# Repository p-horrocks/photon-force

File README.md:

# photon-force

A laser tag implementation using the Particle Photon as the main processor.

# Compiling

To compile this project locally you'll need the gcc-arm toolchain as well as the
Photon firmware. It's built against firmware 0.4.9

* If you get permission problems running npm, see here:
https://docs.npmjs.com/getting-started/fixing-npm-permissions

(On Debian)
> apt-get install gcc-arm-none-eabi dfu_util npm
> npm install -g particle-cli
> git clone https://github.com/spark/firmware.git
> cd firmware
> git checkout release/v0.4.9

Next, create a symlink in firmware/user/applications to where this source is
checked out.

# Flashing

Plug the Photon into a USB port. Once it has powered up, hold down the setup
button then tap the reset button. The status LED will flash magenta for a few
seconds then flash yellow, release the setup button. With the LED flashing
yellow run 'make install' and the firmware will be uploaded using dfu.

# Qt Creator

These files are the Qt Creator project files, they're not needed to compile
the project, they just make is easier to use Qt Creator as the IDE:

  photon-force.config
  photon-force.creator
  photon-force.files
  photon-force.includes

# Gerber generation

From within PCBNew:
- File->Plot
- Plot format: Gerber
- Check Layers
    F.Cu
    B.Cu
    F.SilkS
    B.SilkS
    F.Mask
    B.Mask
    Edge.Cuts
- Check Options
    Plot module value on silkscreen
    Plot module reference on silkscreen
    Plot other module texts on silkscreen
    Exclude PCB edge layer from other layers
    Default line width 0.15mm
- Check Gerber Options
    Use proper filename extensions
- Click 'Plot'
- Click 'Generate Drill File'
- Check Drill Units: Inches
- Check Zeros Format: Decimal format
- Check Drill Map File Format: Gerber
- Check Options: Minimal header
- Check Drill Origin: Absolute
- Click 'Drill File'
- Remove layer names from plot files (so they're all <name>.gXX)
- Rename *.gbr to *.gml
- Rename *.drl to *.txt
- zip with zip -r <zip file> <name>.*
- zip file ready for upload!

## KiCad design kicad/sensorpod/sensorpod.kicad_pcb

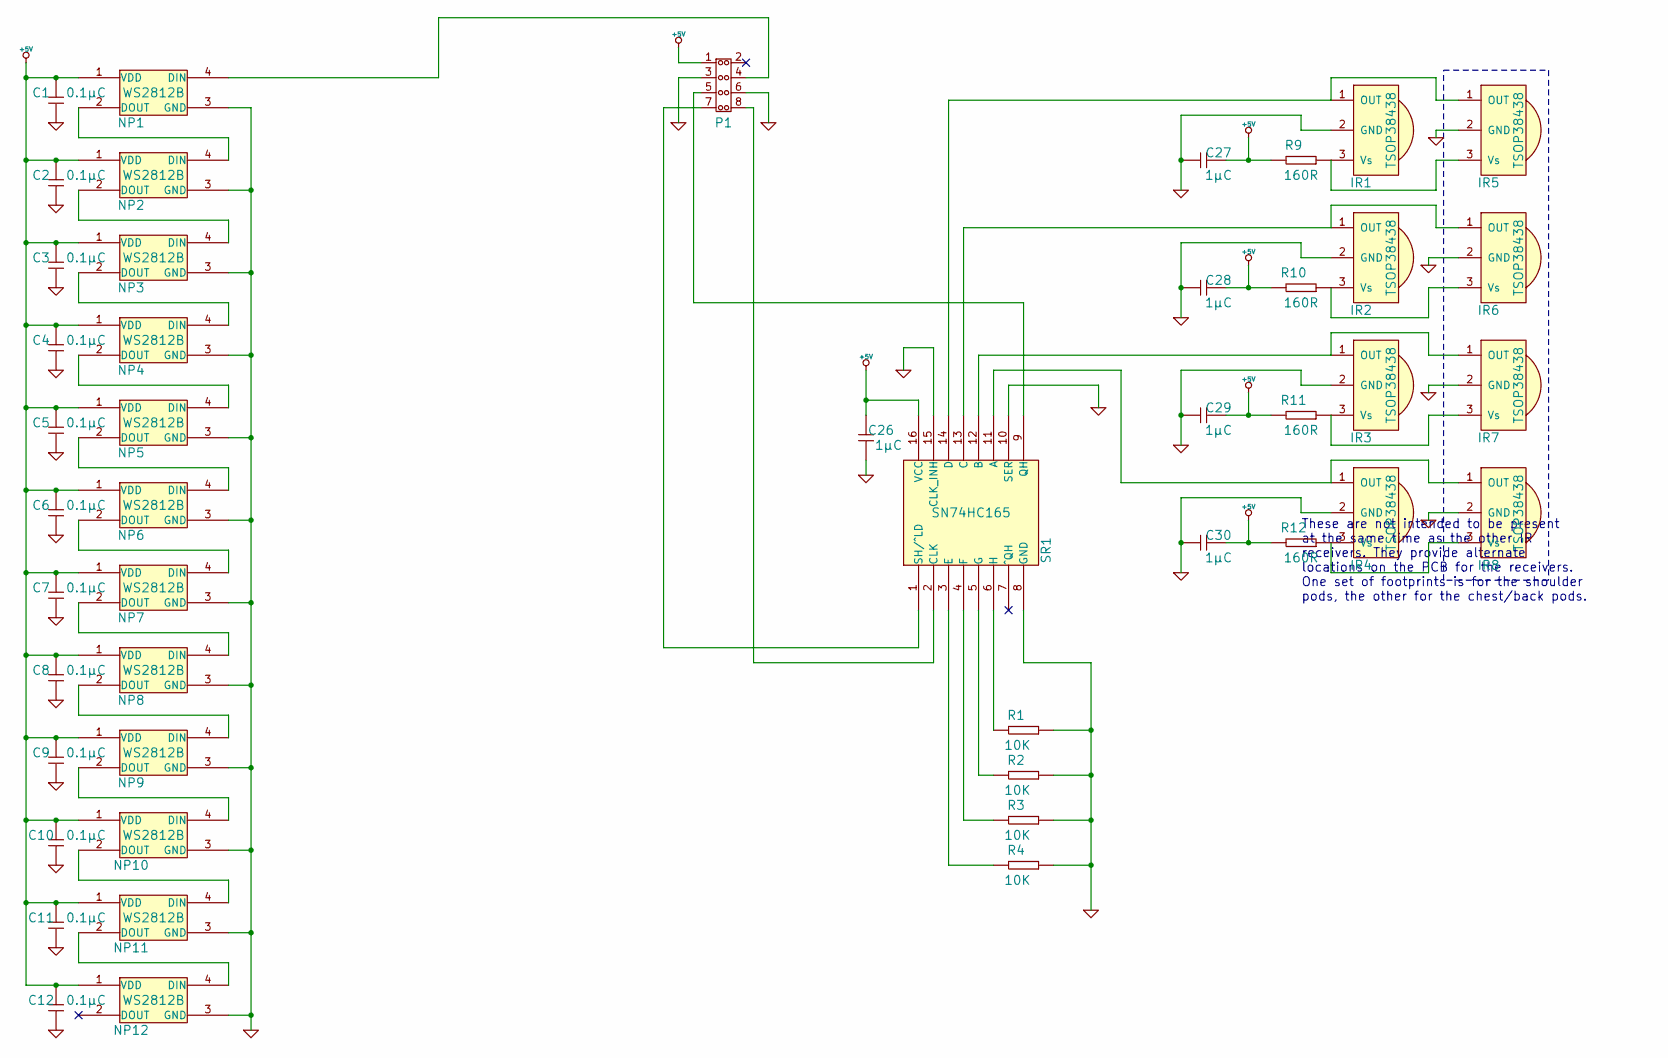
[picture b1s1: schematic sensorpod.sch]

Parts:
C1, C2, C3, C4, C5, C6, C7, C8, C9, C10, C11, C12, C26, C27, C28, C29, C30: GENERIC_CAPACITOR; 0805
IR1, IR2, IR3, IR4, IR5, IR6, IR7, IR8: TSOP38438; Minicast
NP1, NP2, NP3, NP4, NP5, NP6, NP7, NP8, NP9, NP10, NP11, NP12: WS2812B; 5050
P1: HEADER_(8_WAY); Header_4x2
R1, R2, R3, R4, R9, R10, R11, R12: GENERIC_RESISTOR; 0805
SR1: SN74HC165; SOIC-16

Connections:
+5V: C1.1, C2.1, C3.1, C4.1, C5.1, C6.1, C7.1, C8.1, C9.1, C10.1, C11.1, C12.1, C26.1, C27.1, C28.1, C29.1, C30.1, NP1.1 (VDD), NP2.1 (VDD), NP3.1 (VDD), NP4.1 (VDD), NP5.1 (VDD), NP6.1 (VDD), NP7.1 (VDD), NP8.1 (VDD), NP9.1 (VDD), NP10.1 (VDD), NP11.1 (VDD), NP12.1 (VDD), P1.1, R9.1, R10.1, R11.1, R12.1, SR1.16 (VCC)
GND: C1.2, C2.2, C3.2, C4.2, C5.2, C6.2, C7.2, C8.2, C9.2, C10.2, C11.2, C12.2, C26.2, C27.2, C28.2, C29.2, C30.2, IR1.2 (GND), IR2.2 (GND), IR3.2 (GND), IR4.2 (GND), IR5.2 (GND), IR6.2 (GND), IR7.2 (GND), IR8.2 (GND), NP1.3 (GND), NP2.3 (GND), NP3.3 (GND), NP4.3 (GND), NP5.3 (GND), NP6.3 (GND), NP7.3 (GND), NP8.3 (GND), NP9.3 (GND), NP10.3 (GND), NP11.3 (GND), NP12.3 (GND), P1.3, P1.6, R1.2, R2.2, R3.2, R4.2, SR1.8 (GND), SR1.10 (SER), SR1.15 (CLK_INH)
unnamed: P1.8, SR1.2 (CLK)
unnamed: P1.7, SR1.1 (SH/^LD)
unnamed: NP11.2 (DOUT), NP12.4 (DIN)
unnamed: NP10.2 (DOUT), NP11.4 (DIN)
unnamed: IR2.3 (Vs), IR6.3 (Vs), R10.2
unnamed: IR1.1 (OUT), IR5.1 (OUT), SR1.14 (D)
unnamed: IR4.3 (Vs), IR8.3 (Vs), R12.2
unnamed: IR3.3 (Vs), IR7.3 (Vs), R11.2
unnamed: IR1.3 (Vs), IR5.3 (Vs), R9.2
unnamed: IR4.1 (OUT), IR8.1 (OUT), SR1.11 (A)
unnamed: IR3.1 (OUT), IR7.1 (OUT), SR1.12 (B)
unnamed: IR2.1 (OUT), IR6.1 (OUT), SR1.13 (C)
unnamed: NP1.4 (DIN), P1.4
unnamed: R4.1, SR1.3 (E)
unnamed: R3.1, SR1.4 (F)
unnamed: R2.1, SR1.5 (G)
unnamed: R1.1, SR1.6 (H)
unnamed: P1.5, SR1.9 (QH)
unnamed: NP9.2 (DOUT), NP10.4 (DIN)
unnamed: NP5.2 (DOUT), NP6.4 (DIN)
unnamed: NP4.2 (DOUT), NP5.4 (DIN)
unnamed: NP3.2 (DOUT), NP4.4 (DIN)
unnamed: NP2.2 (DOUT), NP3.4 (DIN)
unnamed: NP1.2 (DOUT), NP2.4 (DIN)
unnamed: NP8.2 (DOUT), NP9.4 (DIN)
unnamed: NP7.2 (DOUT), NP8.4 (DIN)
unnamed: NP6.2 (DOUT), NP7.4 (DIN)

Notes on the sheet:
These are not intended to be present at the same time as the other IR receivers. They provide alternate locations on the PCB for the receivers. One set of footprints is for the shoulder pods, the other for the chest/back pods.

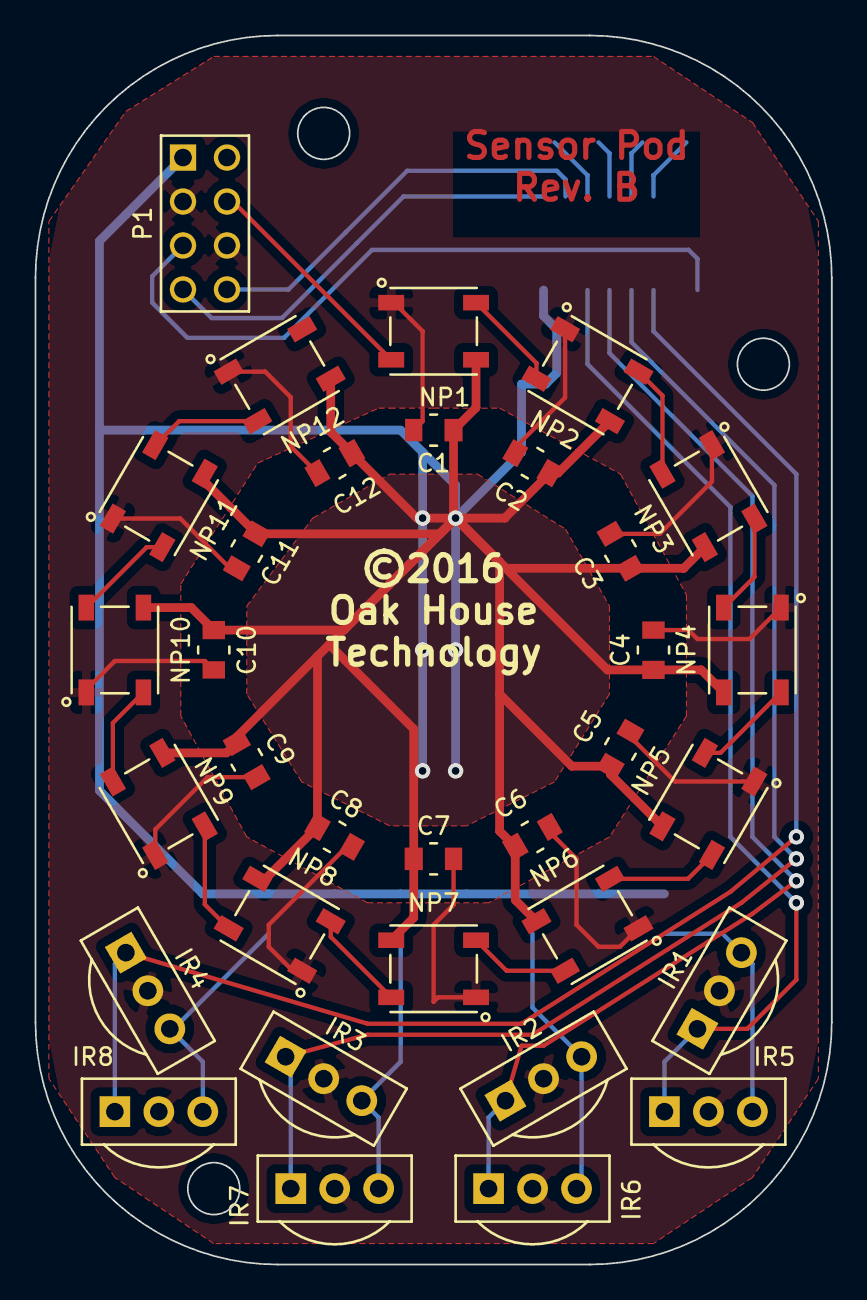
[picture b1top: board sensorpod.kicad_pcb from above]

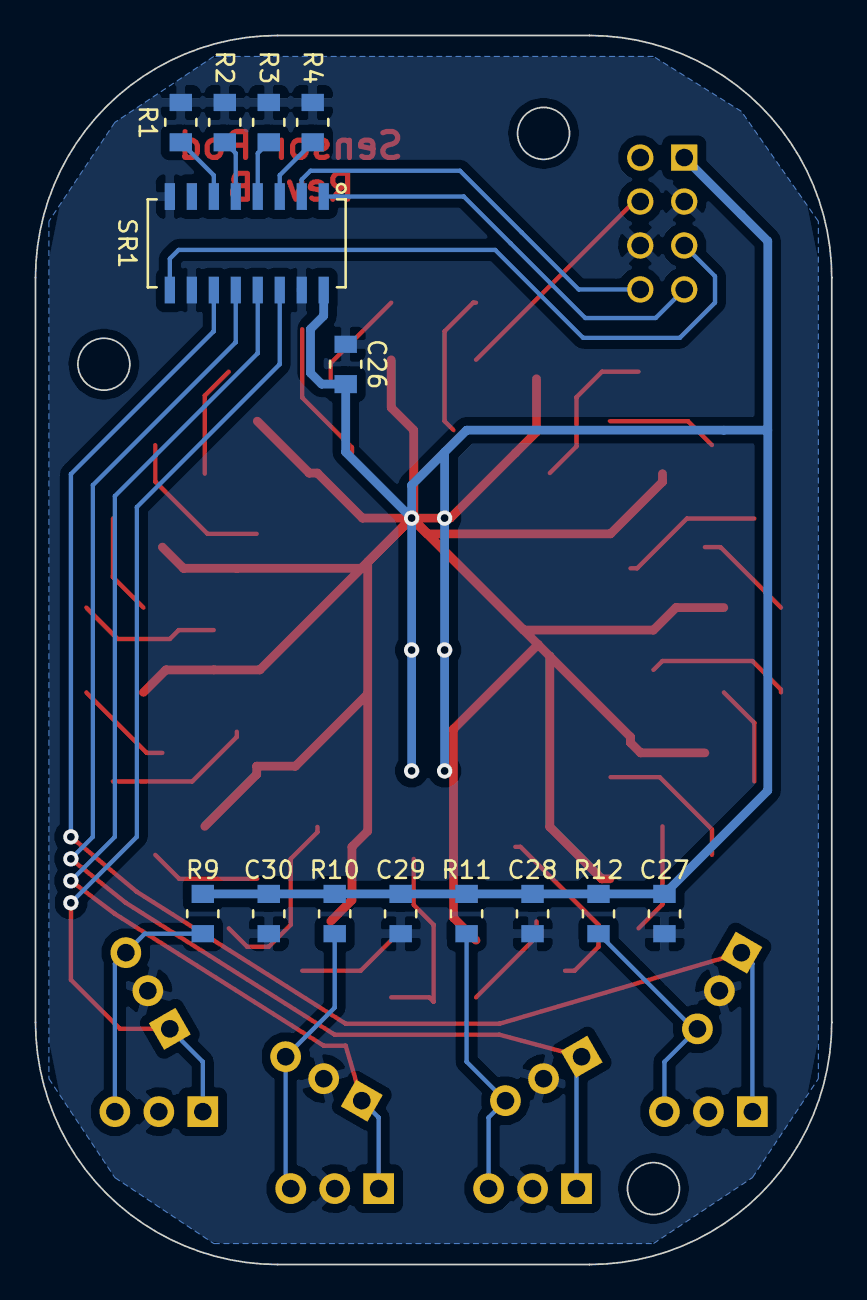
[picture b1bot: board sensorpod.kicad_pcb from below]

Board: 2 copper layers, 46.0 x 71.0 mm, 47 parts (14 on the bottom side), 29 nets.

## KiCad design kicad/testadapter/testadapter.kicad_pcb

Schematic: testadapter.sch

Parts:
P1: HEADER_5X2; Header_5x2
P2, P3, P4, P5: HEADER_(8_WAY); Header_4x2
Q1, Q2, Q3: IRFML8244TRPBF; SOT-23; Part # IRFML8244TRPBF
R1, R2, R3: GENERIC_RESISTOR; 0805

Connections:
+3.3V: P1.2, Q1.1 (G), Q2.1 (G), Q3.1 (G)
+5V: P1.1, P2.1, P3.1, P4.1, P5.1, R1.2, R2.2, R3.2
Clock: P2.8, P3.8, P4.8, P5.8, Q3.3 (D), R3.1
GND: P1.3, P2.3, P2.6, P3.3, P3.6, P4.3, P4.6, P5.3, P5.6
Load: P2.7, P3.7, P4.7, P5.7, Q2.3 (D), R2.1
unnamed: P1.5, Q2.2 (S)
unnamed: P1.4, Q1.2 (S)
unnamed: P1.6, Q3.2 (S)
unnamed: P1.8, P3.5
unnamed: P1.7, P2.5
unnamed: P1.9, P4.5
unnamed: P1.10, P5.5
NeoPixels: P2.4, P3.4, P4.4, P5.4, Q1.3 (D), R1.1

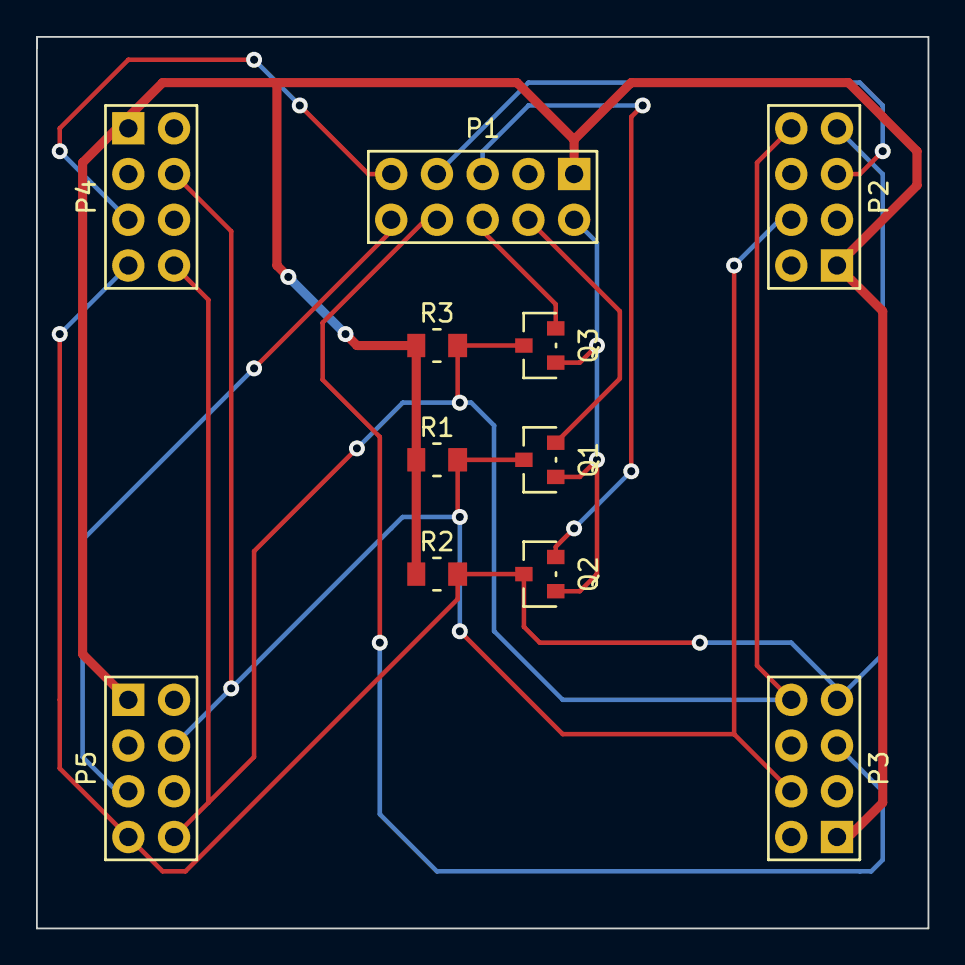
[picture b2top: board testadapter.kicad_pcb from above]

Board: 2 copper layers, 49.5 x 49.5 mm, 11 parts (0 on the bottom side), 13 nets.

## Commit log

2016-01-15 Copied initial code in from Particle Build
2016-01-15 Split main loop into quick iterations
2016-01-16 Added class to manage sending serial data within the main loop without blowing the timing
2016-01-26 Converted serialstream into a namespace so I don't need to mess around with singleton guff just so everyone can access it.
2016-01-26 Started utility namespace for DMA stuff
2016-01-26 Fix compile error
2016-01-26 Allow for different DMA streams
2016-01-26 Use DMA to transfer data to NeoPixels. Main loop runs as fast as possible
2016-01-27 Convert IrReader into (empty) namespace
2016-01-27 Added stub for persistent settings
2016-01-27 Added code for controlling fire rate
2016-01-28 Started on ir emitter thing
2016-01-28 Added number printing
2016-01-28 Starting to debug ir emission
2016-01-30 Use interrupt to handle DMA completion
2016-01-30 Added 600rpm fire rate
2016-01-30 LED colour specified in settings
2016-01-30 Got audio working
2016-02-05 Added makefile to do local build with local firmware checkout
2016-02-05 Added Qt Creator project files and makefile for local build
2016-02-05 Remove used variable
2016-02-05 Use DFU for programming
2016-02-05 Updated file names to work with local build
2016-02-06 Added IR sending. Lots of debugging still included since it doesn't work yet
2016-02-07 Started putting in reading of IR via parallel-serial register
2016-02-13 Starting on schematic
2016-02-13 NeoPixel string in the schematic
2016-02-16 Sensor pos schematic done
2016-02-18 Split command pod and sensor pod into separate kicad projects
    They'll end up being separate PCBs, so separate projects makes sense
2016-02-18 Started putting in footprints for sensorpod
2016-02-18 Fixed up use of common parts library
2016-02-18 Added footprints for sensorpod
2016-02-20 Sensor pod footprints all in
2016-02-22 Initial sensor pod PCB
2016-02-22 Reduced component count so it will fit
2016-02-23 Swap a few cable pins
2016-02-23 Prototype sensor pod PCB complete
2016-02-26 Updated sensorpod schematic and PCB to fit into Serpac C9 enclosure
2016-02-28 Comment change
2016-02-28 Adding parts for command pod
2016-02-29 Remove vibration motor from sensor pos - it will just be in the command pod
2016-02-29 Added part number field to all components
2016-03-01 Updated pin assignments to allow for i2c haptic controller
2016-03-02 Added SPDT switch, put in ir emitter with power switch
2016-03-02 Moved shift register to allow more room for cable entry
2016-03-02 More work on command pod
2016-03-03 Added heirarchial schematics for command pod
2016-03-03 Annotated schematics
2016-03-03 Can't remember
2016-03-04 Updated BOM
2016-03-06 Moved source files into subdirectory
2016-03-06 Added task list
2016-03-07 Put in charging circuit
2016-03-07 More stuff
2016-03-13 Updated prices with actual purchase price
2016-03-13 Added github standard kicad gitignore
2016-03-20 Updated neopixel supply
2016-07-12 Minor tweaks
2016-07-19 Created script to simplify the generation of PCB manufacturing package
2016-07-19 Added extra vias to central 5V fill
2016-07-20 Update BOM
2016-09-17 Reduce neopix count to match hardware
2016-09-17 update notes
2016-09-17 Added red flash for death
2016-09-17 Can not receive ir codes
2016-09-20 Corrected wrong pad assignment on ir receiver footprint
2016-09-20 Added start of adapter for testing
2016-09-20 5x2 header
2016-09-21 Created adapter PCB for testing sensorpods
2016-09-21 Put in alternate IR receiver locations on sensor pod
    Should make things easier when the pins need to be bent to lie them
    flat on the chest/back pods

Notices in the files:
kicad/sensorpod/sensorpod.kicad_pcb:
©2016
